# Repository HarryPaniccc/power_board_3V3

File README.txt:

This project is a modular battery management board meant to support an 18650 lithium-ion battery while providing 3.3V at an output pin.

It should manage power, battery health, charging, and regulation.

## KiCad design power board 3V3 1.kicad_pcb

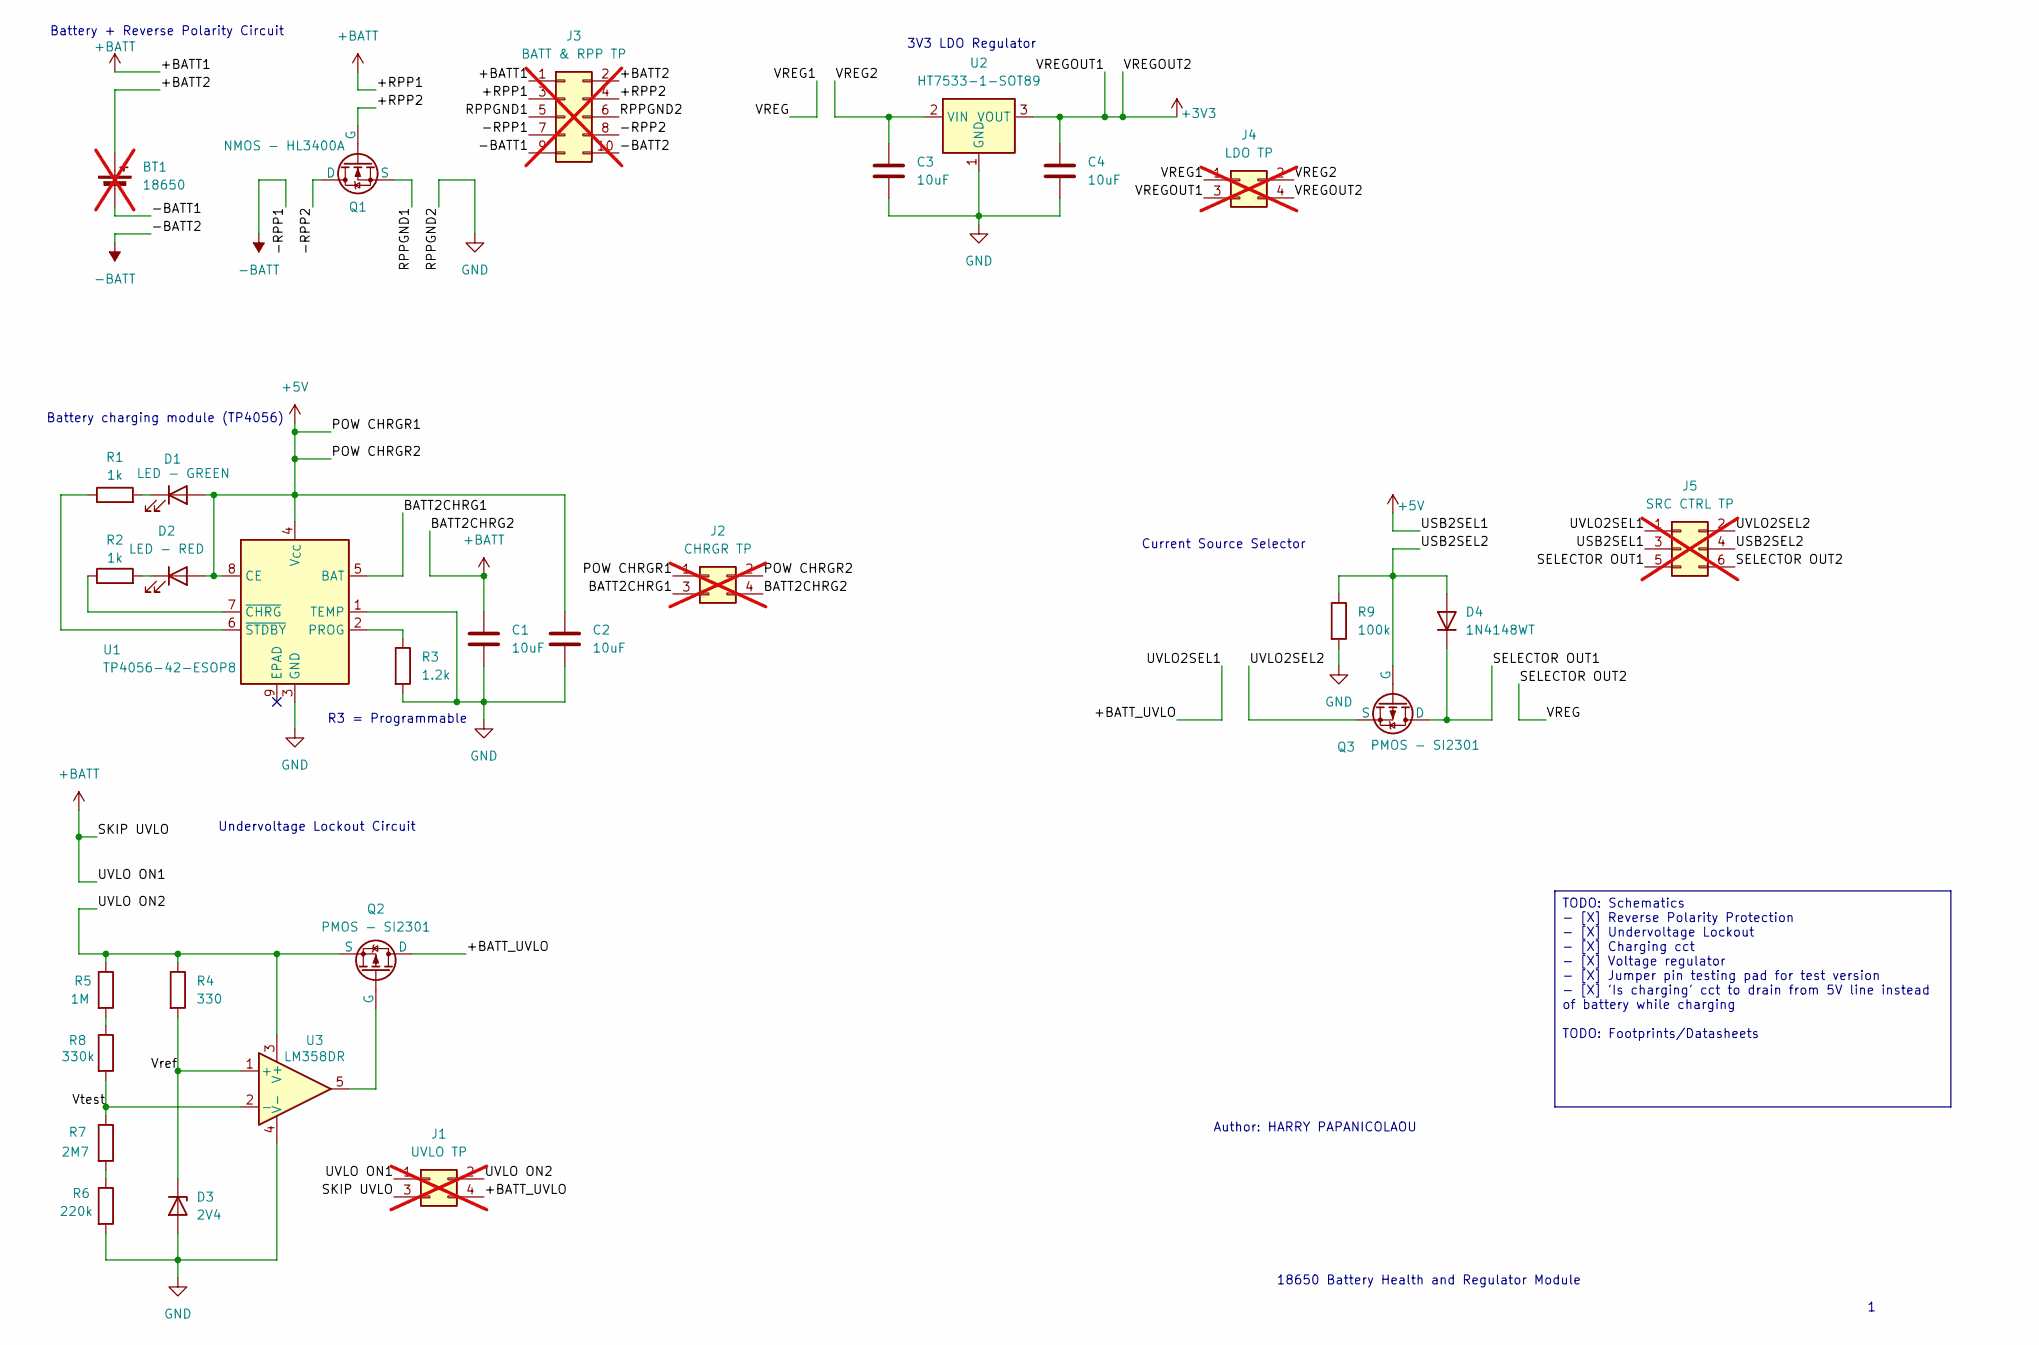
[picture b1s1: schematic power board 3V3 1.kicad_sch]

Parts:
BT1: 18650; PinHeader_1x02_P2.54mm_Vertical; not fitted
C1, C2, C3, C4: 10uF; C_0201_0603Metric
D1: LED - GREEN; LED_0805_2012Metric
D2: LED - RED; LED_0805_2012Metric
D3: 2V4; D_SOD-523
D4: 1N4148WT; D_SOD-523
J1: UVLO TP; PinSocket_2x02_P2.54mm_Vertical; not fitted
J2: CHRGR TP; PinSocket_2x02_P2.54mm_Vertical; not fitted
J3: BATT & RPP TP; PinSocket_2x05_P2.54mm_Vertical; not fitted
J4: LDO TP; PinSocket_2x02_P2.54mm_Vertical; not fitted
J5: SRC CTRL TP; PinSocket_2x03_P2.54mm_Vertical; not fitted
Q1: NMOS - HL3400A; SOT-23
Q2, Q3: PMOS - SI2301; SOT-23
R1, R2: 1k; R_0201_0603Metric
R3: 1.2k; R_0201_0603Metric
R4: 330; R_0201_0603Metric
R5: 1M; R_0201_0603Metric
R6: 220k; R_0201_0603Metric
R7: 2M7; R_0201_0603Metric
R8: 330k; R_0201_0603Metric
R9: 100k; R_0201_0603Metric
U1: TP4056-42-ESOP8; SOIC-8-1EP_3.9x4.9mm_P1.27mm_EP2.41x3.3mm_ThermalVias
U2: HT7533-1-SOT89; SOT-89-3
U3: LM358DR; SOIC-8-1EP_3.9x4.9mm_P1.27mm_EP2.29x3mm

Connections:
+3V3: C4.1, J4.3, J4.4, U2.3 (VOUT)
+5V: C2.1, D1.2 (A), D2.2 (A), J2.1, J2.2, J5.3, U1.4 (V_{CC}), U1.8 (CE)
+BATT: C1.1, J1.1, J1.3, J2.4, J3.1, J3.3
-BATT: J3.7, J3.10
/+BATT2: BT1.1 (+), J3.2
/+BATT_UVLO: J1.4, J5.1, Q2.1 (D)
/+RPP2: J3.4, Q1.2 (G)
/-BATT1: BT1.2 (-), J3.9
/-RPP2: J3.8, Q1.1 (D)
/BATT2CHRG1: J2.3, U1.5 (BAT)
/RPPGND1: J3.5, Q1.3 (S)
/SELECTOR OUT1: D4.1 (K), J5.5, Q3.1 (D)
/SELECTOR OUT2: J4.1, J5.6
/USB2SEL2: D4.2 (A), J5.4, Q3.2 (G), R9.1
/UVLO2SEL2: J5.2, Q3.3 (S)
/UVLO ON2: J1.2, Q2.3 (S), R4.1, R5.1, U3.3 (V+)
/VREG2: C3.1, J4.2, U2.2 (VIN)
/Vref: D3.1 (K), R4.2, U3.1 (+)
/Vtest: R7.1, R8.2, U3.2 (-)
GND: C1.2, C2.2, C3.2, C4.2, D3.2 (A), J3.6, R3.2, R6.2, R9.2, U1.1 (TEMP), U1.3 (GND), U2.1 (GND), U3.4 (V-)
unnamed: D1.1 (K), R1.2
unnamed: D2.1 (K), R2.2
unnamed: Q2.2 (G), U3.5
unnamed: R5.2, R8.1
unnamed: R6.1, R7.2
unnamed: R3.1, U1.2 (PROG)
unnamed: R2.1, U1.7 (~CHRG)
unnamed: R1.1, U1.6 (~STDBY)

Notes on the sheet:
Current Source Selector
18650 Battery Health and Regulator Module
Undervoltage Lockout Circuit
Battery + Reverse Polarity Circuit
R3 = Programmable
Author: HARRY PAPANICOLAOU
3V3 LDO Regulator
Battery charging module (TP4056)
TODO: Schematics - [X] Reverse Polarity Protection - [X] Undervoltage Lockout - [X] Charging cct - [X] Voltage regulator - [X] Jumper pin testing pad for test version - [X] 'Is charging' cct to drain from 5V line instead of battery while charging TODO: Footprints/Datasheets

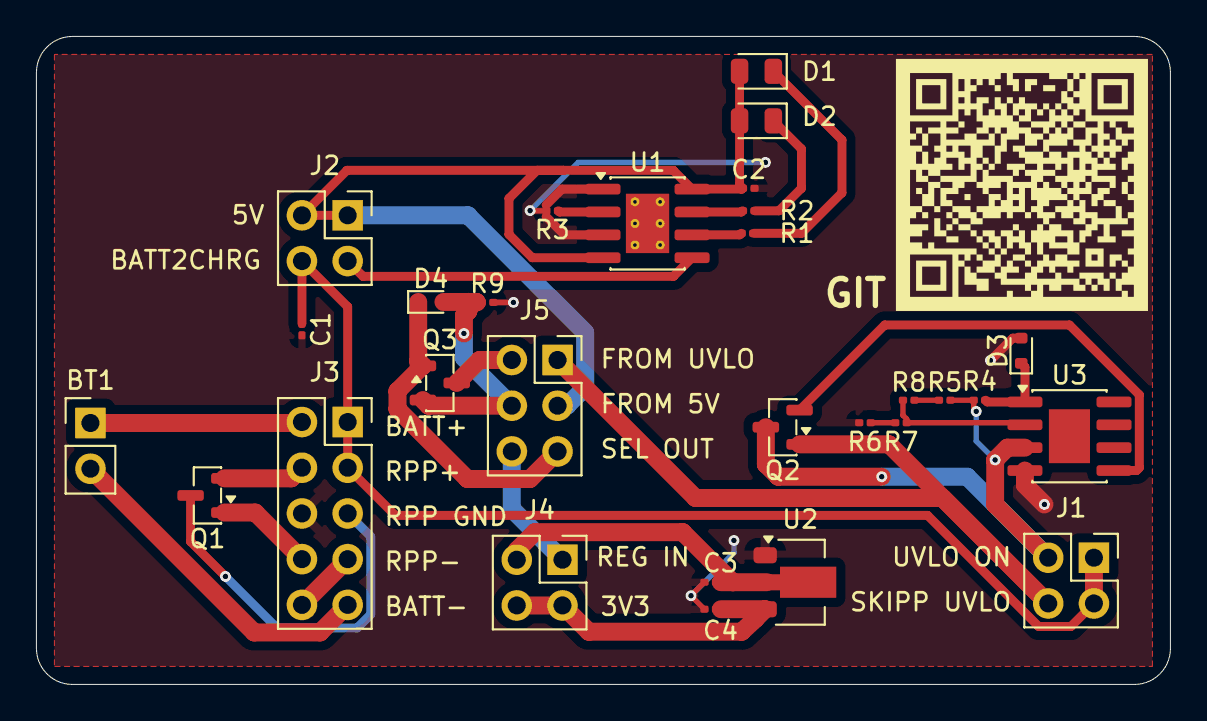
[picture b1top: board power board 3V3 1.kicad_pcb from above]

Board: 2 copper layers, 63.0 x 36.0 mm, 30 parts (0 on the bottom side), 28 nets.

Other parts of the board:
GIT: LOGO

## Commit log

2026-03-05 First commit and README
2026-03-05 Almost done schema
2026-03-05 Small progress
2026-03-06 This grunt work slaps idk why people dont do more PCBs
2026-03-11 Almost ready to do PCB
2026-03-17 Last footprint then pcb
2026-03-18 UGH im washed
2026-03-19 Next is just silk screen labelling and ask Si Teng if Im retarded
2026-03-19 Moved test pads
2026-03-20 Something something
2026-03-20 PCB looks better now
2026-03-20 Routing fixed
2026-03-20 Labels done
2026-03-20 idk why we need to do this push
2026-03-20 Added silkscreen github link
2026-03-25 Discord died
